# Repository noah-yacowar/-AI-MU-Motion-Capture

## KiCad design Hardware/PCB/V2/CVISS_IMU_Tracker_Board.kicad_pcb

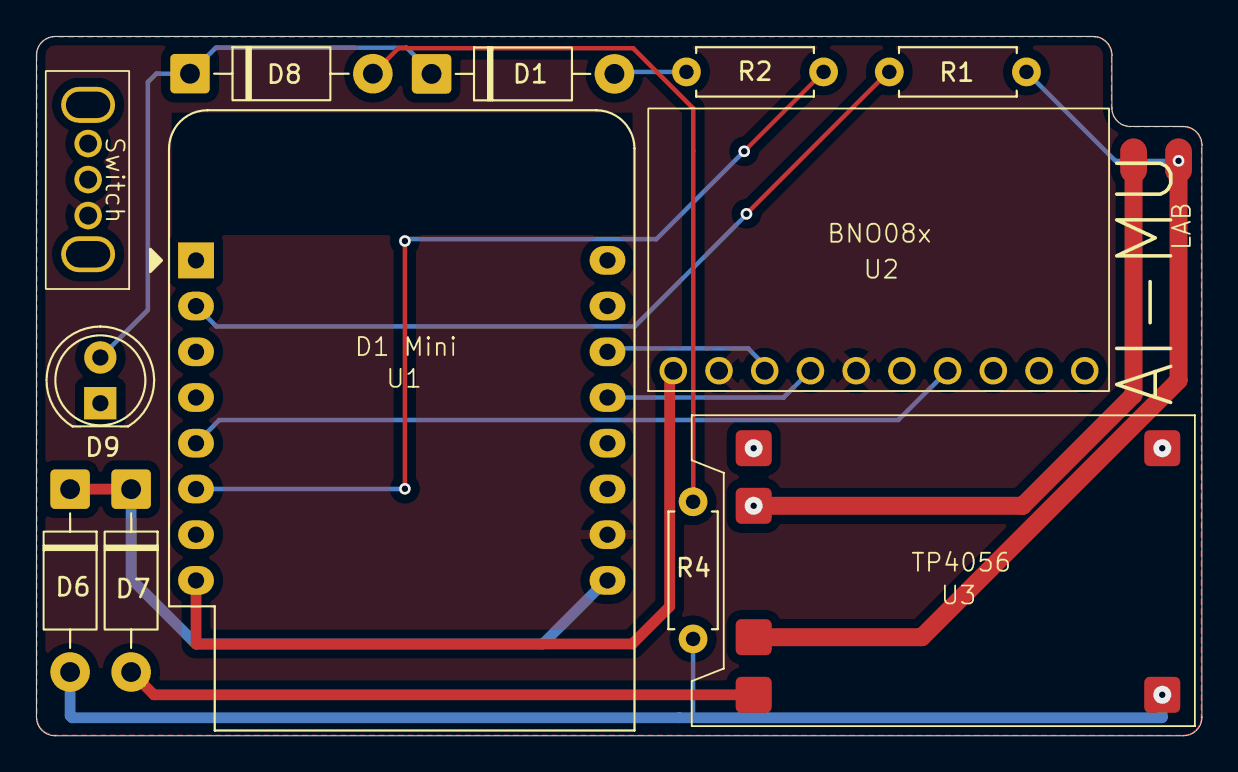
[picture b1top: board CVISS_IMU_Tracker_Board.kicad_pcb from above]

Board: 2 copper layers, 64.7 x 38.9 mm, 13 parts (0 on the bottom side), 15 nets.

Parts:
D1, D6, D7, D8: 1N5817; D_DO-41_SOD81_P10.16mm_Horizontal
D9: Blue LED; LED_D5.0mm_Clear
R1: 180R; R_Axial_DIN0207_L6.3mm_D2.5mm_P7.62mm_Horizontal
R2: 200R; R_Axial_DIN0207_L6.3mm_D2.5mm_P7.62mm_Horizontal
R4: 1kR; R_Axial_DIN0207_L6.3mm_D2.5mm_P7.62mm_Horizontal
SW1: SW_SPST; SK12DO7_Switch
U1: WEMOS_D1_mini; WEMOS_D1_mini_light
U2: BNO08x_Board
U3: TP4056_Board
U4: Battery_Connector

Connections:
+3.3V: U1.8 (3V3), U2.1 (VCC)
+5V: D6.1 (K), D7.1 (K), U1.9 (5V)
/B+: R1.2, U3.2 (B+), U4.1 (+)
/GP_LED: D1.1 (K), D8.1 (K), D9.2 (A)
/IN+: D6.2 (A), R4.1, U3.5 (IN+)
/INT: U1.5 (MISO/D6), U2.7 (INT)
/OUT+: D7.2 (A), U3.1 (OUT+)
/PWR_LED: D8.2 (A), R4.2
/SCL: U1.14 (SCL/D1), U2.3 (SCL)
/SDA: U1.13 (SDA/D2), U2.4 (SDA)
/SW_GND: SW1.2 (B), U1.10 (GND), U2.2 (GND), U2.5 (ADO)
GND: D9.1 (K), SW1.1 (A), U3.3 (B-), U3.4 (OUT-), U3.6 (IN-), U4.2 (-)
unnamed: D1.2 (A), R2.2
unnamed: R1.1, U1.2 (A0)
unnamed: R2.1, U1.6 (MOSI/D7)

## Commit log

2025-08-20 Hardware commit
2025-08-20 firmware
2025-08-29 minor fixing
